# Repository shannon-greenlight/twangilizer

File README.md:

# Twangilizer - 4 Harmonic Tracking Oscillator with 4 VCAs
Twangilizer is a 20HP Eurorack module designed and made by Greenface Labs.
Used in conjunction with a VCO and a multiple-output CV generating module such as the Bonkulator, Twangilizer is a great way to set the amplitude envelopes of a tone and 4 of its harmonics. 
The harmonics are selectable from 1f, 2f, 3f, 4f, 5f, 6f, 7f and 8f. They are available as square waves at the output jacks 1-4.
The harmonics are also used to generate 10-step sine-wave approximations. The amplitudes of these waves are set by the CV inputs and then added to form the analog signal output.

Twangilizer features one signal input, an analog signal output, 4 digital harmonic outputs, 4 CV bias level adjustment pots, and four CV inputs to the VCAs.
It also features harmonic selection controls: Four 8 position rotary switches to select the harmonic from the above list. And there is a toggle switch per channel that selects divide by one, or divide by two.

The signal input level must be greater than .1Vp-p for the phase-locked loop circuits to be able to lock on.
The output signal ranges from 0 to 10Vp-p. The CV inputs range is 0 - 10V.

These repos contain the materials needed to construct the Twangilizer main board and the front panel. The files are for KiCAD 6.0. 
Go to the Greenlight Kicad repo to get the needed libraries. The gerber files work with JLCPC and will most likely work with other board manufacturers.

When using the JLCPCB assembly service, the BOM is split into 3 parts.
- bom/lcsc/main_bom.xlsx : The parts to be assembled by JLCPCB
- bom/digi-key/main_split.xlsx : The remaining parts to be assembled by user
- bom/other/other_bom.xlsx : The parts that must be bought from sources other than JLCPCB and Digi-Key

Also, when an assembly service is used, a component position file is required. This file's path is: fab/main_cpl.xlsx

notes: 	The cpl files are auto-generated from the .pos files produced by KiCAD. The bom files are generated by generate_boms.bat. You will need to refresh the data and save the file when changes to 
the schematic that affect the BOM or changes to the board layout occur. 
If they exist, the extra parts and additional data fields that appear on the schematic help to produce the different BOM files. 
They must be maintained for these BOMs to come out right.

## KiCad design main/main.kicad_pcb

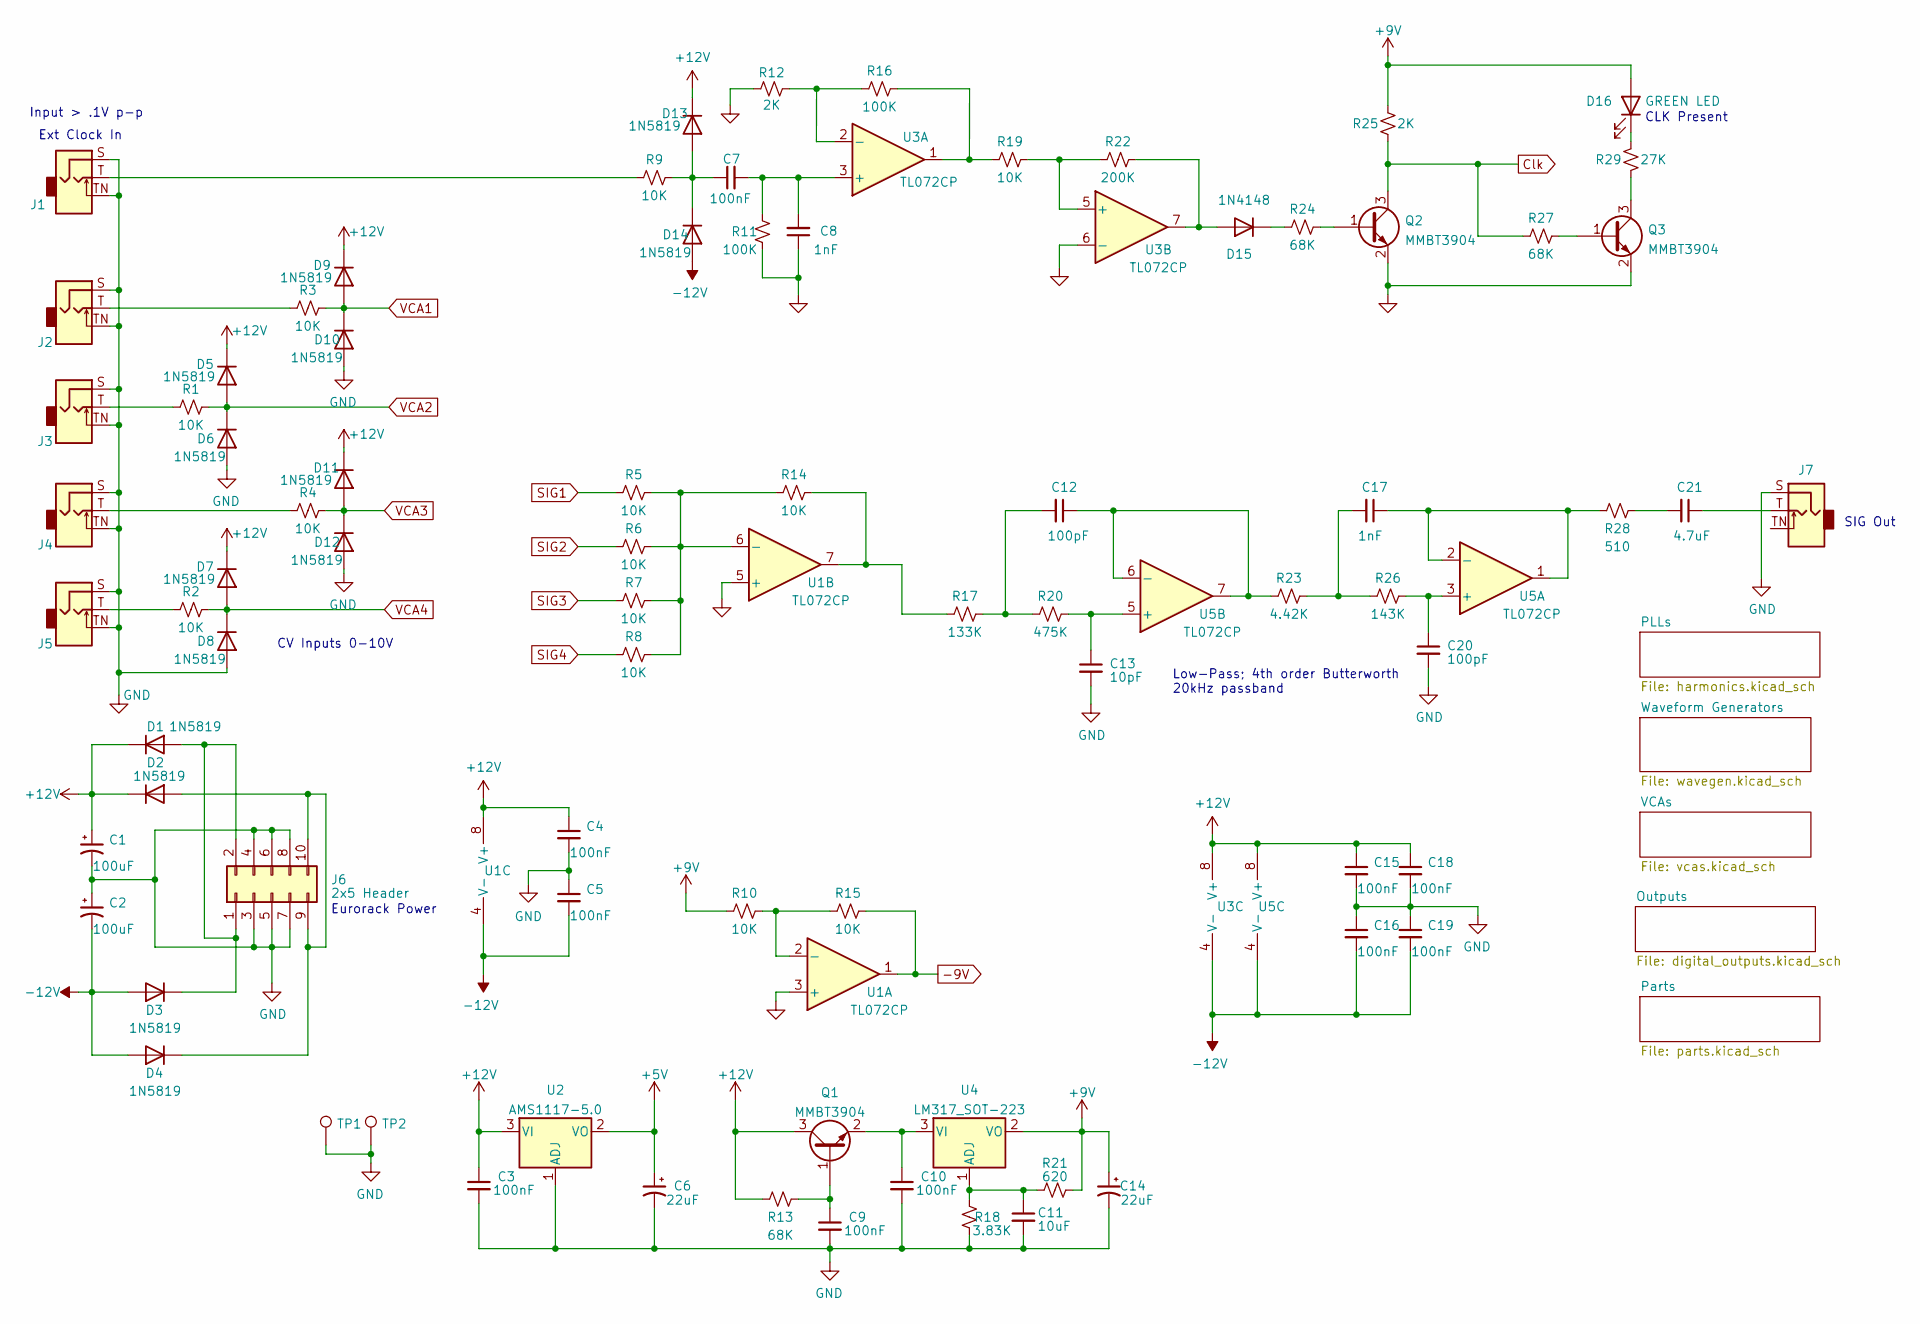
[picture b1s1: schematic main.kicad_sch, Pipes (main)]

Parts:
C1, C2: 100uF; CP_Elec_6.3x5.4_Nichicon; Digi-Key Part 399-EDH107M016A9GAACT-ND
C3, C4, C5, C7, C9, C10, C15, C16, C18, C19: 100nF; C_0805_2012Metric_Pad1.18x1.45mm_HandSolder; Digi-Key Part 478-10836-1-ND
C6, C14: 22uF; CP_EIA-3216-18_Kemet-A; Digi-Key Part 478-12960-1-ND
C8, C17: 1nF; C_0805_2012Metric_Pad1.18x1.45mm_HandSolder; Digi-Key Part 399-9877-1-ND
C11: 10uF; C_0805_2012Metric_Pad1.18x1.45mm_HandSolder; Digi-Key Part 399-9886-1-ND
C12, C20: 100pF; C_0805_2012Metric_Pad1.18x1.45mm_HandSolder; Digi-Key Part 399-9877-1-ND
C13: 10pF; C_0603_1608Metric_Pad1.08x0.95mm_HandSolder; Digi-Key Part 399-9877-1-ND
C21: 4.7uF; C_1206_3216Metric; Digi-Key Part 399-9877-1-ND
D1, D2, D3, D4, D5, D6, D7, D8, D9, D10, D11, D12, D13, D14: 1N5819; D_SOD-323_HandSoldering; Digi-Key Part 478-7800-1-ND
D15: 1N4148; D_SOD-123; Digi-Key Part 1N4148VSCT-ND
D16: GREEN LED; LED_D3.0mm; Digi-Key Part 732-5007-ND
J1, J2, J3, J4, J5, J7: 3.5mm Jack; Jack_3.5mm_QingPu_WQP-PJ398SM_Vertical; Digi-Key Part WM17366-ND
J6: 2x5 Header; PinHeader_2x05_P2.54mm_Vertical_SMD; LCSC Part # C124391
Q1, Q2, Q3: MMBT3904; SOT-23; LCSC Part # C20526
R1, R2, R3, R4, R5, R6, R7, R8, R9, R10, R14, R15, R19: 10K; R_0603_1608Metric; Digi-Key Part CRT0805-FZ-1002ELFCT-ND
R11, R16: 100K; R_0805_2012Metric_Pad1.20x1.40mm_HandSolder; Digi-Key Part CF14JT10K0CT-ND
R12, R25: 2K; R_0603_1608Metric; Digi-Key Part CRT0805-FZ-1002ELFCT-ND
R13: 68K; R_0805_2012Metric_Pad1.20x1.40mm_HandSolder; Digi-Key Part CF14JT68K0CT-ND
R17: 133K; R_0603_1608Metric; Digi-Key Part CRT0805-FZ-1002ELFCT-ND
R18: 3.83K; R_0805_2012Metric_Pad1.20x1.40mm_HandSolder; Digi-Key Part CF14JT68K0CT-ND
R20: 475K; R_0603_1608Metric; Digi-Key Part CRT0805-FZ-1002ELFCT-ND
R21: 620; R_0805_2012Metric_Pad1.20x1.40mm_HandSolder; Digi-Key Part CF14JT68K0CT-ND
R22: 200K; R_0805_2012Metric_Pad1.20x1.40mm_HandSolder; Digi-Key Part CF14JT10K0CT-ND
R23: 4.42K; R_0603_1608Metric; Digi-Key Part CRT0805-FZ-1002ELFCT-ND
R24, R27: 68K; R_0805_2012Metric_Pad1.20x1.40mm_HandSolder; Digi-Key Part CF14JT10K0CT-ND
R26: 143K; R_0603_1608Metric; Digi-Key Part CRT0805-FZ-1002ELFCT-ND
R28: 510; R_0805_2012Metric_Pad1.20x1.40mm_HandSolder; Digi-Key Part PPC470W-1CT-ND
R29: 27K; R_0805_2012Metric_Pad1.20x1.40mm_HandSolder; Digi-Key Part CRT0805-FZ-1002ELFCT-ND
TP1, TP2: TestPoint; TestPoint_Keystone_5005-5009_Compact; Digi-Key Part 36-5006-ND
U1, U3, U5: TL072CP; SOIC-8_3.9x4.9mm_P1.27mm; Digi-Key Part 296-1775-5-ND
U2: AMS1117-5.0; SOT-223-3_TabPin2; LCSC Part # C6187
U4: LM317_SOT-223; SOT-223-3_TabPin2; LCSC Part # C347367

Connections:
+5V: C6.1, U2.2 (VO); also elsewhere on the board
+9V: C14.1, D16.2 (A), R10.2, R21.1, R25.1, U4.2 (VO); also elsewhere on the board
+12V: C1.1, C3.1, C4.1, C15.1, C18.1, D1.1 (K), D2.1 (K), D5.1 (K), D7.1 (K), D9.1 (K), D11.1 (K), D13.1 (K), Q1.3 (C), R13.2, U1.8 (V+), U2.3 (VI), U3.8 (V+), U5.8 (V+); also elsewhere on the board
-9V: R15.1, U1.1; also elsewhere on the board
-12V: C2.2, C5.2, C16.2, C19.2, D3.2 (A), D4.2 (A), D14.2 (A), U1.4 (V-), U3.4 (V-), U5.4 (V-); also elsewhere on the board
Clk: Q2.3 (C), R25.2, R27.2; also elsewhere on the board
GND: C1.2, C2.1, C3.2, C4.2, C5.1, C6.2, C8.1, C9.2, C10.2, C11.2, C13.2, C14.2, C15.2, C16.1, C18.2, C19.1, C20.2, D6.2 (A), D8.2 (A), D10.2 (A), D12.2 (A), J1.S, J1.TN, J2.S, J2.TN, J3.S, J3.TN, J4.S, J4.TN, J5.S, J5.TN, J6.3, J6.4, J6.5, J6.6, J6.7, J6.8, J7.S, Q2.2 (E), Q3.2 (E), R11.2, R12.1, R18.2, TP1.1, TP2.1, U1.3 (+), U1.5 (+), U2.1 (ADJ), U3.6 (-); also elsewhere on the board
unnamed: C7.1, D13.2 (A), D14.1 (K), R9.1
unnamed: C7.2, C8.2, R11.1, U3.3 (+)
unnamed: C9.1, Q1.1 (B), R13.1
unnamed: C10.1, Q1.2 (E), U4.3 (VI)
unnamed: C11.1, R18.1, R21.2, U4.1 (ADJ)
unnamed: C12.1, R23.2, U5.6 (-), U5.7
unnamed: C12.2, R17.1, R20.2
unnamed: C13.1, R20.1, U5.5 (+)
unnamed: C17.1, R28.1, U5.1, U5.2 (-)
unnamed: C17.2, R23.1, R26.2
unnamed: C20.1, R26.1, U5.3 (+)
unnamed: C21.1, J7.T
unnamed: C21.2, R28.2
unnamed: D1.2 (A), D3.1 (K), J6.1, J6.2
unnamed: D2.2 (A), D4.1 (K), J6.9, J6.10
unnamed: D15.1 (K), R24.2
unnamed: D15.2 (A), R22.1, U3.7
unnamed: D16.1 (K), R29.2
unnamed: J1.T, R9.2
unnamed: J2.T, R3.2
unnamed: J3.T, R1.2
unnamed: J4.T, R4.2
unnamed: J5.T, R2.2
unnamed: Q2.1 (B), R24.1
unnamed: Q3.1 (B), R27.1
unnamed: Q3.3 (C), R29.1
unnamed: R10.1, R15.2, U1.2 (-)
unnamed: R12.2, R16.2, U3.2 (-)
unnamed: R14.1, R17.2, U1.7
unnamed: R5.1, R6.1, R7.1, R8.1, R14.2, U1.6 (-)
unnamed: R16.1, R19.2, U3.1
unnamed: R19.1, R22.2, U3.5 (+)
SIG1: R5.2; also elsewhere on the board
SIG2: R6.2; also elsewhere on the board
SIG3: R7.2; also elsewhere on the board
SIG4: R8.2; also elsewhere on the board
VCA1: D9.2 (A), D10.1 (K), R3.1; also elsewhere on the board
VCA2: D5.2 (A), D6.1 (K), R1.1; also elsewhere on the board
VCA3: D11.2 (A), D12.1 (K), R4.1; also elsewhere on the board
VCA4: D7.2 (A), D8.1 (K), R2.1; also elsewhere on the board

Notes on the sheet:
Eurorack Power
SIG Out
Low-Pass; 4th order Butterworth 20kHz passband
Input > .1V p-p
CLK Present
CV Inputs 0-10V
Ext Clock In

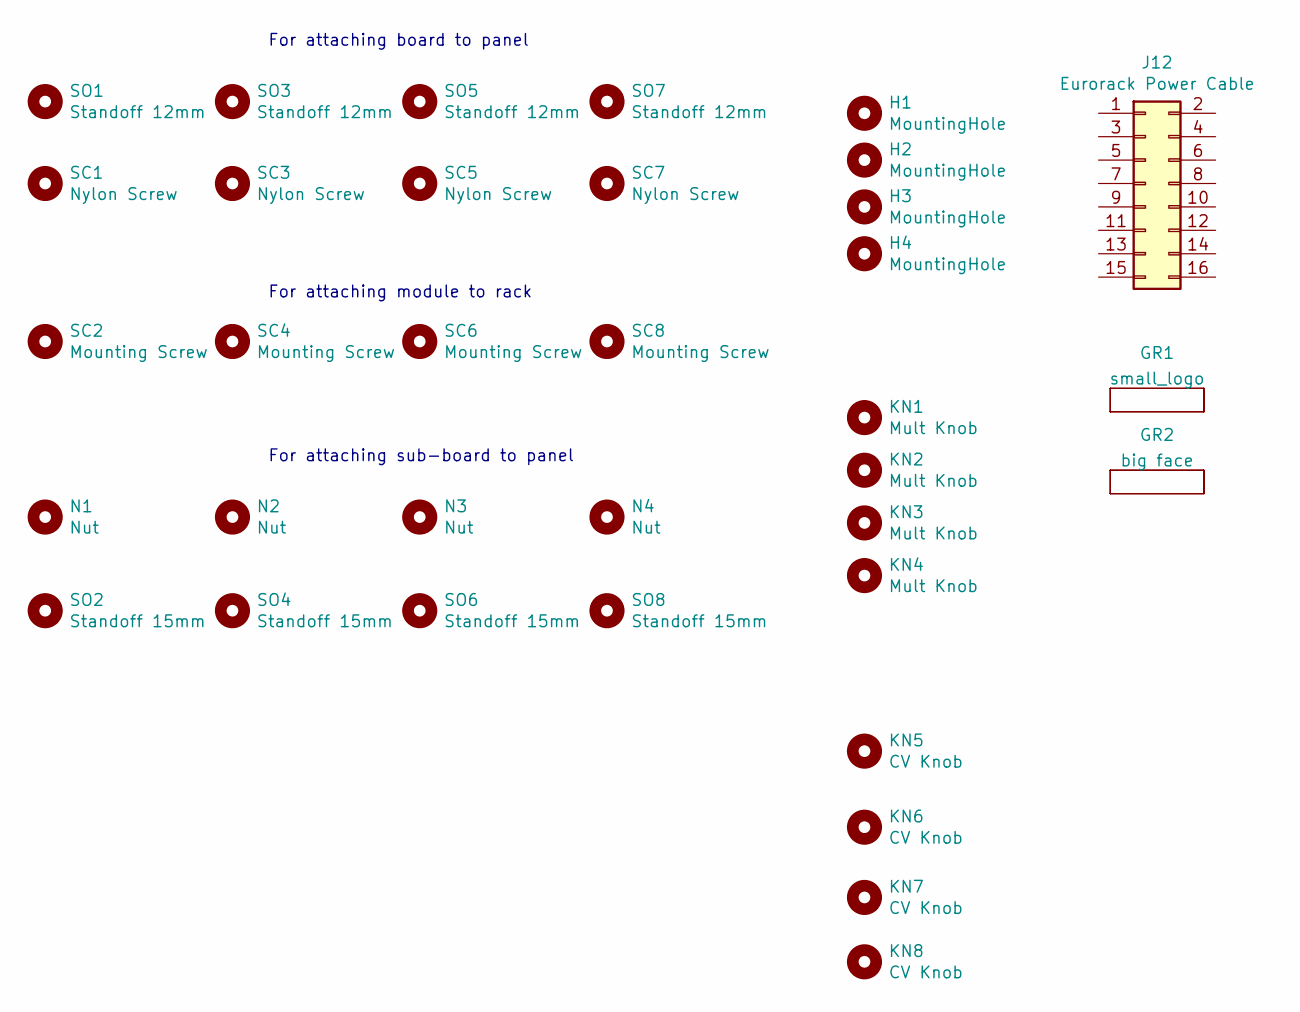
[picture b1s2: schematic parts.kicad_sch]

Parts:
GR1: small_logo; small_face
GR2: big face; face_logo
H1, H2, H3, H4: MountingHole; MountingHole_2.5mm
J12: Eurorack Power Cable; Digi-Key Part H3CCS-1618G-ND
KN1, KN2, KN3, KN4: Mult Knob; Digi-Key Part 1722-1314-ND
KN5, KN6, KN7, KN8: CV Knob; Digi-Key Part 4654-FC7251-ND
N1, N2, N3, N4: Nut; Digi-Key Part 36-4687-ND
SC1, SC3, SC5, SC7: Nylon Screw; Digi-Key Part 36-29331-ND
SC2, SC4, SC6, SC8: Mounting Screw; Digi-Key Part 335-1156-ND
SO1, SO3, SO5, SO7: Standoff 12mm; Digi-Key Part 732-13063-ND
SO2, SO4, SO6, SO8: Standoff 15mm; Digi-Key Part 732-13072-ND

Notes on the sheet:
For attaching module to rack
For attaching board to panel
For attaching sub-board to panel

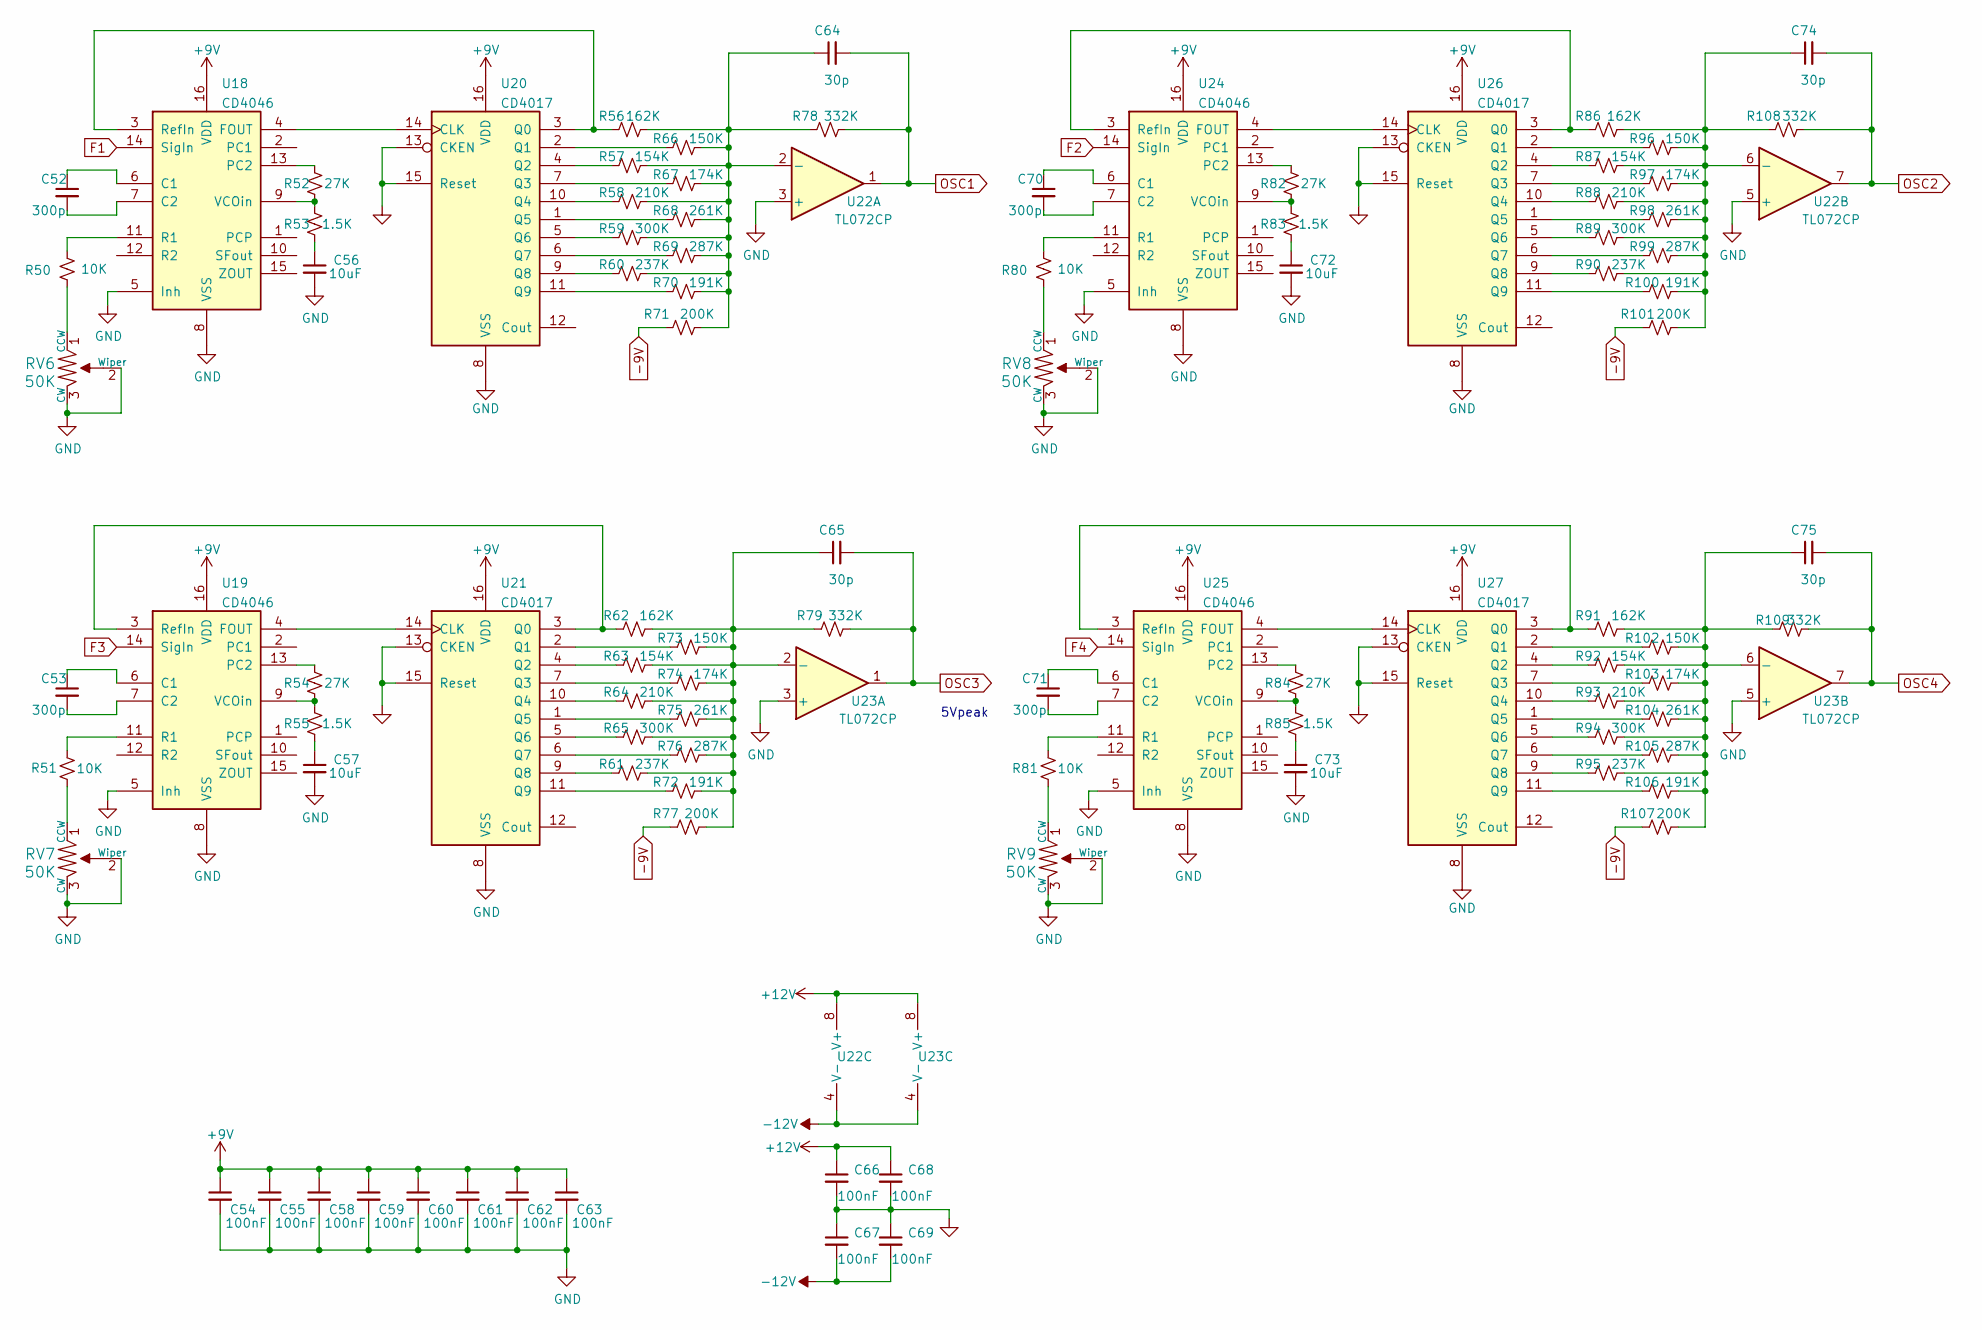
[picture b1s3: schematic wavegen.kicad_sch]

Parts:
C52, C53, C70, C71: 300p; C_0603_1608Metric_Pad1.08x0.95mm_HandSolder; Digi-Key Part BC2662CT-ND
C54, C55, C58, C59, C60, C61, C62, C63, C66, C67, C68, C69: 100nF; C_0805_2012Metric_Pad1.18x1.45mm_HandSolder; Digi-Key Part 478-10836-1-ND
C56, C57, C72, C73: 10uF; C_0805_2012Metric_Pad1.18x1.45mm_HandSolder; Digi-Key Part 478-10836-1-ND
C64, C65, C74, C75: 30p; C_0603_1608Metric_Pad1.08x0.95mm_HandSolder; Digi-Key Part BC2662CT-ND
R50, R51, R80, R81: 10K; R_0603_1608Metric; Digi-Key Part CF14JT10K0CT-ND
R52, R54, R82, R84: 27K; R_0805_2012Metric_Pad1.20x1.40mm_HandSolder; Digi-Key Part CF14JT10K0CT-ND
R53, R55, R83, R85: 1.5K; R_0805_2012Metric_Pad1.20x1.40mm_HandSolder; Digi-Key Part CF14JT10K0CT-ND
R56, R62, R86, R91: 162K; R_0603_1608Metric; Digi-Key Part CF14JT10K0CT-ND
R57, R63, R87, R92: 154K; R_0603_1608Metric; Digi-Key Part CF14JT10K0CT-ND
R58, R64, R88, R93: 210K; R_0603_1608Metric; Digi-Key Part CF14JT10K0CT-ND
R59, R65, R89, R94: 300K; R_0603_1608Metric; Digi-Key Part CF14JT10K0CT-ND
R60, R61, R90, R95: 237K; R_0603_1608Metric; Digi-Key Part CF14JT10K0CT-ND
R66, R73, R96, R102: 150K; R_0603_1608Metric; Digi-Key Part CF14JT10K0CT-ND
R67, R74, R97, R103: 174K; R_0603_1608Metric; Digi-Key Part CF14JT10K0CT-ND
R68, R75, R98, R104: 261K; R_0603_1608Metric; Digi-Key Part CF14JT10K0CT-ND
R69, R76, R99, R105: 287K; R_0603_1608Metric; Digi-Key Part CF14JT10K0CT-ND
R70, R72, R100, R106: 191K; R_0603_1608Metric; Digi-Key Part CF14JT10K0CT-ND
R71, R77, R101, R107: 200K; R_0603_1608Metric; Digi-Key Part CF14JT10K0CT-ND
R78, R79, R108, R109: 332K; R_0603_1608Metric; Digi-Key Part CF14JT10K0CT-ND
RV6, RV7, RV8, RV9: 50K; Potentiometer_Bourns_3224W_Vertical; Digi-Key Part 490-2881-ND
U18, U19, U24, U25: CD4046; TSSOP-16_4.4x5mm_P0.65mm; LCSC Part # C2651240
U20, U21, U26, U27: CD4017; SOIC-16_3.9x9.9mm_P1.27mm; Digi-Key Part 296-12808-1-ND
U22, U23: TL072CP; SOIC-8_3.9x4.9mm_P1.27mm; Digi-Key Part 296-1775-5-ND

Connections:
+9V: C54.1, C55.1, C58.1, C59.1, C60.1, C61.1, C62.1, C63.1, U18.16 (VDD), U19.16 (VDD), U20.16 (VDD), U21.16 (VDD), U24.16 (VDD), U25.16 (VDD), U26.16 (VDD), U27.16 (VDD); also elsewhere on the board
+12V: C66.1, C68.1, U22.8 (V+), U23.8 (V+); also elsewhere on the board
-9V: R71.1, R77.1, R101.1, R107.1; also elsewhere on the board
-12V: C67.2, C69.2, U22.4 (V-), U23.4 (V-); also elsewhere on the board
F1: U18.14 (SigIn); also elsewhere on the board
F2: U24.14 (SigIn); also elsewhere on the board
F3: U19.14 (SigIn); also elsewhere on the board
F4: U25.14 (SigIn); also elsewhere on the board
GND: C54.2, C55.2, C56.2, C57.2, C58.2, C59.2, C60.2, C61.2, C62.2, C63.2, C66.2, C67.1, C68.2, C69.1, C72.2, C73.2, RV6.2 (Wiper), RV6.3 (CW), RV7.2 (Wiper), RV7.3 (CW), RV8.2 (Wiper), RV8.3 (CW), RV9.2 (Wiper), RV9.3 (CW), U18.5 (Inh), U18.8 (VSS), U19.5 (Inh), U19.8 (VSS), U20.8 (VSS), U20.13 (CKEN), U20.15 (Reset), U21.8 (VSS), U21.13 (CKEN), U21.15 (Reset), U22.3 (+), U22.5 (+), U23.3 (+), U23.5 (+), U24.5 (Inh), U24.8 (VSS), U25.5 (Inh), U25.8 (VSS), U26.8 (VSS), U26.13 (CKEN), U26.15 (Reset), U27.8 (VSS), U27.13 (CKEN), U27.15 (Reset); also elsewhere on the board
unnamed: C52.1, U18.6 (C1)
unnamed: C52.2, U18.7 (C2)
unnamed: C53.1, U19.6 (C1)
unnamed: C53.2, U19.7 (C2)
unnamed: C56.1, R53.2
unnamed: C57.1, R55.2
unnamed: C64.1, R56.2, R57.2, R58.2, R59.2, R60.2, R66.2, R67.2, R68.2, R69.2, R70.2, R71.2, R78.1, U22.2 (-)
unnamed: C65.1, R61.2, R62.2, R63.2, R64.2, R65.2, R72.2, R73.2, R74.2, R75.2, R76.2, R77.2, R79.1, U23.2 (-)
unnamed: C70.1, U24.6 (C1)
unnamed: C70.2, U24.7 (C2)
unnamed: C71.1, U25.6 (C1)
unnamed: C71.2, U25.7 (C2)
unnamed: C72.1, R83.2
unnamed: C73.1, R85.2
unnamed: C74.1, R86.2, R87.2, R88.2, R89.2, R90.2, R96.2, R97.2, R98.2, R99.2, R100.2, R101.2, R108.1, U22.6 (-)
unnamed: C75.1, R91.2, R92.2, R93.2, R94.2, R95.2, R102.2, R103.2, R104.2, R105.2, R106.2, R107.2, R109.1, U23.6 (-)
unnamed: R50.1, U18.11 (R1)
unnamed: R50.2, RV6.1 (CCW)
unnamed: R51.1, U19.11 (R1)
unnamed: R51.2, RV7.1 (CCW)
unnamed: R52.1, U18.13 (PC2)
unnamed: R52.2, R53.1, U18.9 (VCOin)
unnamed: R54.1, U19.13 (PC2)
unnamed: R54.2, R55.1, U19.9 (VCOin)
unnamed: R56.1, U18.3 (RefIn), U20.3 (Q0)
unnamed: R57.1, U20.4 (Q2)
unnamed: R58.1, U20.10 (Q4)
unnamed: R59.1, U20.5 (Q6)
unnamed: R60.1, U20.9 (Q8)
unnamed: R61.1, U21.9 (Q8)
unnamed: R62.1, U19.3 (RefIn), U21.3 (Q0)
unnamed: R63.1, U21.4 (Q2)
unnamed: R64.1, U21.10 (Q4)
unnamed: R65.1, U21.5 (Q6)
unnamed: R66.1, U20.2 (Q1)
unnamed: R67.1, U20.7 (Q3)
unnamed: R68.1, U20.1 (Q5)
unnamed: R69.1, U20.6 (Q7)
unnamed: R70.1, U20.11 (Q9)
unnamed: R72.1, U21.11 (Q9)
unnamed: R73.1, U21.2 (Q1)
unnamed: R74.1, U21.7 (Q3)
unnamed: R75.1, U21.1 (Q5)
unnamed: R76.1, U21.6 (Q7)
unnamed: R80.1, U24.11 (R1)
unnamed: R80.2, RV8.1 (CCW)
unnamed: R81.1, U25.11 (R1)
unnamed: R81.2, RV9.1 (CCW)
unnamed: R82.1, U24.13 (PC2)
unnamed: R82.2, R83.1, U24.9 (VCOin)
unnamed: R84.1, U25.13 (PC2)
unnamed: R84.2, R85.1, U25.9 (VCOin)
unnamed: R86.1, U24.3 (RefIn), U26.3 (Q0)
unnamed: R87.1, U26.4 (Q2)
unnamed: R88.1, U26.10 (Q4)
unnamed: R89.1, U26.5 (Q6)
unnamed: R90.1, U26.9 (Q8)
unnamed: R91.1, U25.3 (RefIn), U27.3 (Q0)
unnamed: R92.1, U27.4 (Q2)
unnamed: R93.1, U27.10 (Q4)
unnamed: R94.1, U27.5 (Q6)
unnamed: R95.1, U27.9 (Q8)
unnamed: R96.1, U26.2 (Q1)
unnamed: R97.1, U26.7 (Q3)
unnamed: R98.1, U26.1 (Q5)
unnamed: R99.1, U26.6 (Q7)
unnamed: R100.1, U26.11 (Q9)
unnamed: R102.1, U27.2 (Q1)
unnamed: R103.1, U27.7 (Q3)
unnamed: R104.1, U27.1 (Q5)
unnamed: R105.1, U27.6 (Q7)
unnamed: R106.1, U27.11 (Q9)
unnamed: U18.4 (FOUT), U20.14 (CLK)
unnamed: U19.4 (FOUT), U21.14 (CLK)
unnamed: U24.4 (FOUT), U26.14 (CLK)
unnamed: U25.4 (FOUT), U27.14 (CLK)
OSC1: C64.2, R78.2, U22.1; also elsewhere on the board
OSC2: C74.2, R108.2, U22.7; also elsewhere on the board
OSC3: C65.2, R79.2, U23.1; also elsewhere on the board
OSC4: C75.2, R109.2, U23.7; also elsewhere on the board

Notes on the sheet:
5Vpeak

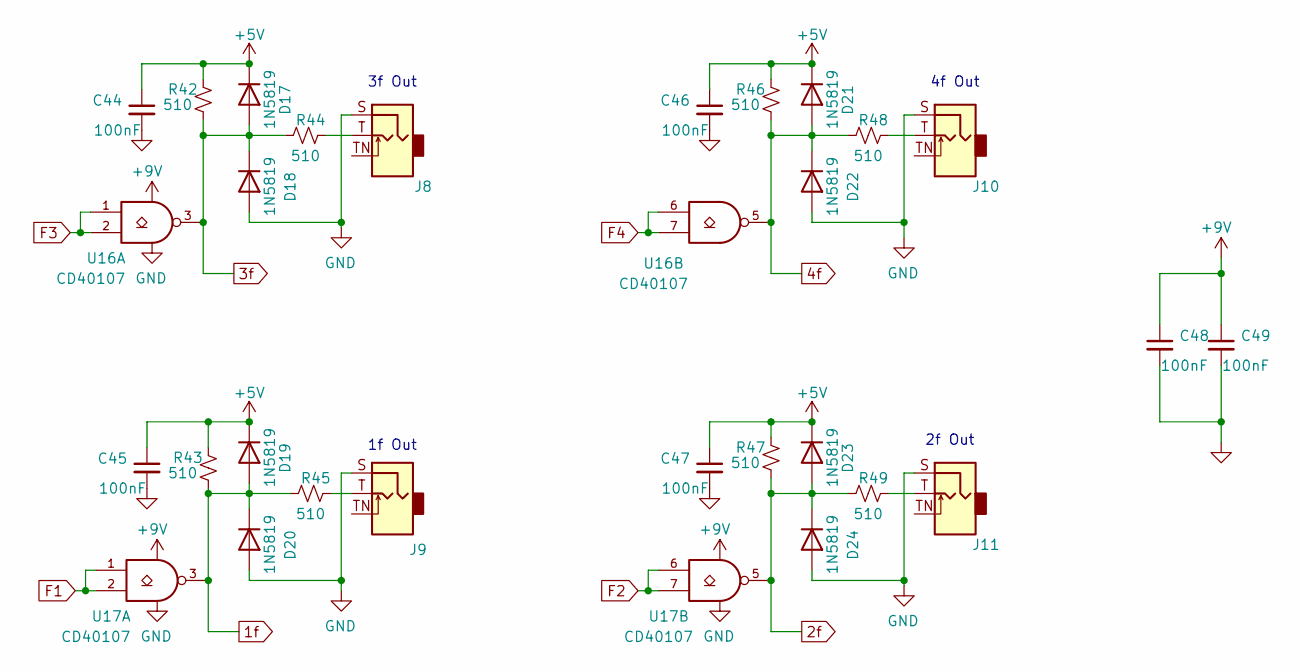
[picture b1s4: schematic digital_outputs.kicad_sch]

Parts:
C44, C45, C46, C47, C48, C49: 100nF; C_0805_2012Metric_Pad1.18x1.45mm_HandSolder; Digi-Key Part 478-10836-1-ND
D17, D18, D19, D20, D21, D22, D23, D24: 1N5819; D_SOD-323_HandSoldering; Digi-Key Part 478-7800-1-ND
J8, J9, J10, J11: 3.5mm Jack; Jack_3.5mm_QingPu_WQP-PJ398SM_Vertical; Digi-Key Part WM17366-ND
R42, R43, R46, R47: 510; R_0805_2012Metric_Pad1.20x1.40mm_HandSolder; Digi-Key Part PPC470W-1CT-ND
R44, R45, R48, R49: 510; R_0805_2012Metric_Pad1.20x1.40mm_HandSolder; Digi-Key Part CRT0805-FZ-1002ELFCT-ND
U16, U17: CD40107; SOIC-8_3.9x4.9mm_P1.27mm; LCSC Part # C2691402

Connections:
1f: D19.2 (A), D20.1 (K), R43.1, R45.2, U17.3
2f: D23.2 (A), D24.1 (K), R47.1, R49.2, U17.5
3f: D17.2 (A), D18.1 (K), R42.1, R44.2, U16.3
4f: D21.2 (A), D22.1 (K), R46.1, R48.2, U16.5
+5V: C44.1, C45.1, C46.1, C47.1, D17.1 (K), D19.1 (K), D21.1 (K), D23.1 (K), R42.2, R43.2, R46.2, R47.2; also elsewhere on the board
+9V: C48.1, C49.1, U16.8 (VCC), U17.8 (VCC); also elsewhere on the board
F1: U17.1, U17.2; also elsewhere on the board
F2: U17.6, U17.7; also elsewhere on the board
F3: U16.1, U16.2; also elsewhere on the board
F4: U16.6, U16.7; also elsewhere on the board
GND: C44.2, C45.2, C46.2, C47.2, C48.2, C49.2, D18.2 (A), D20.2 (A), D22.2 (A), D24.2 (A), J8.S, J9.S, J10.S, J11.S, U16.4 (GND), U17.4 (GND); also elsewhere on the board
unnamed: J8.T, R44.1
unnamed: J9.T, R45.1
unnamed: J10.T, R48.1
unnamed: J11.T, R49.1

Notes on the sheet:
2f Out
4f Out
3f Out
1f Out

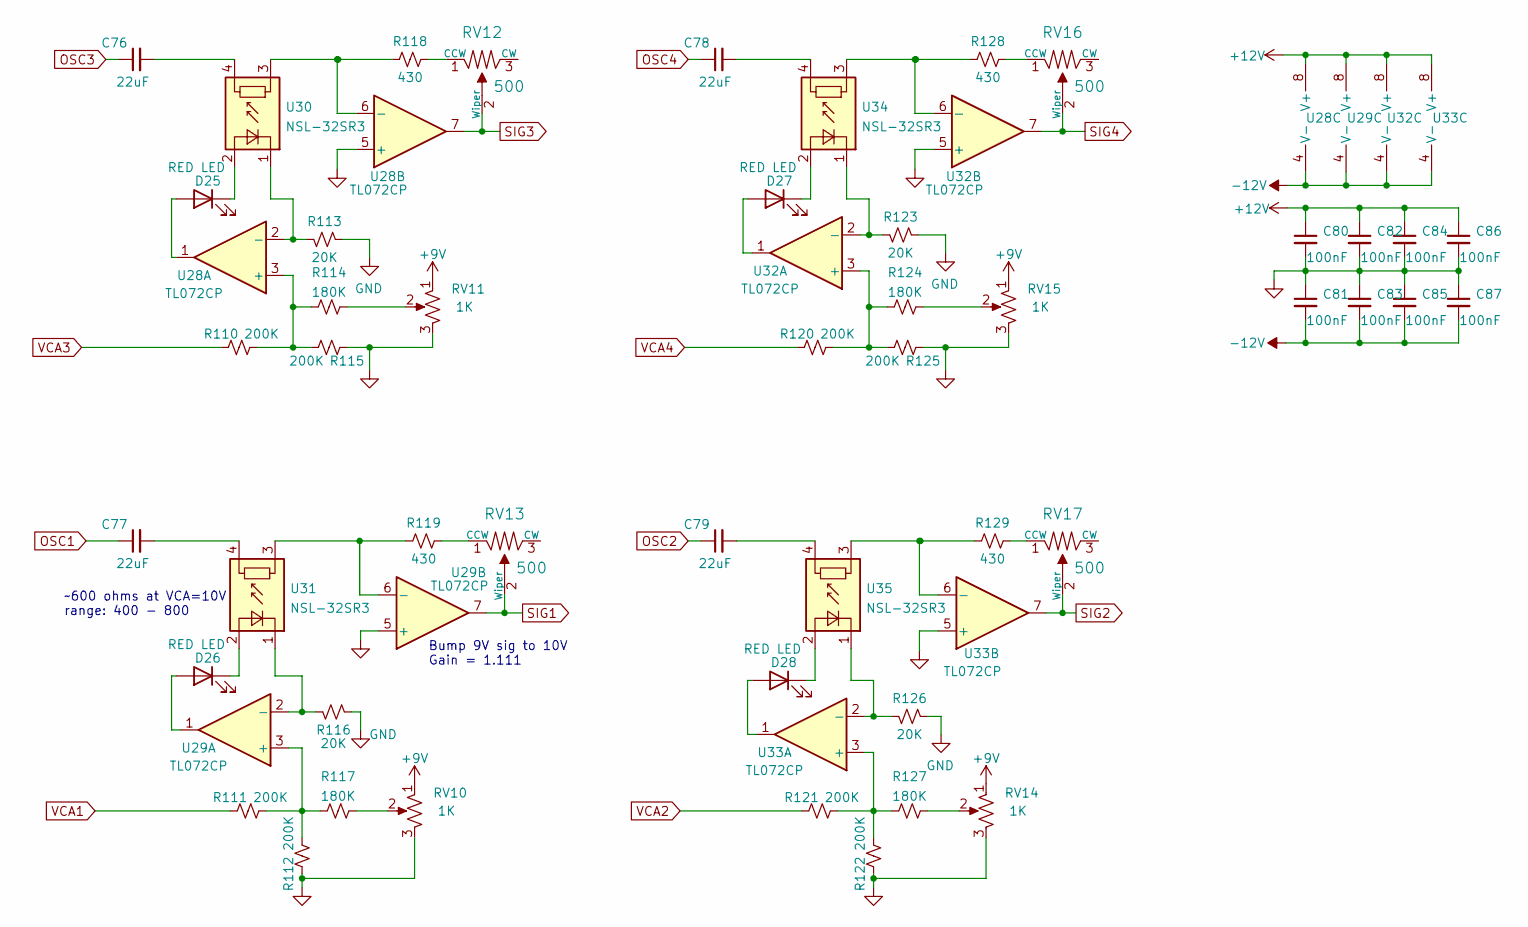
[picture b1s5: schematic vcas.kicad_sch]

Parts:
C76, C77, C78, C79: 22uF; C_0805_2012Metric_Pad1.18x1.45mm_HandSolder; Digi-Key Part 478-10836-1-ND
C80, C81, C82, C83, C84, C85, C86, C87: 100nF; C_0805_2012Metric_Pad1.18x1.45mm_HandSolder; Digi-Key Part 478-10836-1-ND
D25, D26, D27, D28: RED LED; LED_D3.0mm; Digi-Key Part 732-5005-ND
R110, R111, R112, R115, R120, R121, R122, R125: 200K; R_0603_1608Metric; Digi-Key Part CF14JT10K0CT-ND
R113, R116, R123, R126: 20K; R_0603_1608Metric; Digi-Key Part CRT0805-FZ-1002ELFCT-ND
R114, R117, R124, R127: 180K; R_0603_1608Metric; LCSC Part # C3016400
R118, R119, R128, R129: 430; R_0603_1608Metric; Digi-Key Part CRT0805-FZ-1002ELFCT-ND
RV10, RV11, RV14, RV15: 1K; Potentiometer_Bourns_PTV09A-1_Single_Vertical; Digi-Key Part PTV09A-4225F-B102-ND
RV12, RV13, RV16, RV17: 500; Potentiometer_Bourns_3224W_Vertical; LCSC Part # C116324
U28: TL072CP; SOIC-8_3.9x4.9mm_P1.27mm; LCSC Part # C6961
U29, U32, U33: TL072CP; SOIC-8_3.9x4.9mm_P1.27mm; Digi-Key Part 296-1775-5-ND
U30, U31, U34, U35: NSL-32SR3; Digi-Key Part NSL-32SR3-ND

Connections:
+9V: RV10.1, RV11.1, RV14.1, RV15.1; also elsewhere on the board
+12V: C80.1, C82.1, C84.1, C86.1, U28.8 (V+), U29.8 (V+), U32.8 (V+), U33.8 (V+); also elsewhere on the board
-12V: C81.2, C83.2, C85.2, C87.2, U28.4 (V-), U29.4 (V-), U32.4 (V-), U33.4 (V-); also elsewhere on the board
GND: C80.2, C81.1, C82.2, C83.1, C84.2, C85.1, C86.2, C87.1, R112.1, R113.2, R115.1, R116.2, R122.1, R123.2, R125.1, R126.2, RV10.3, RV11.3, RV14.3, RV15.3, U28.5 (+), U29.5 (+), U32.5 (+), U33.5 (+); also elsewhere on the board
unnamed: C76.2, U30.4
unnamed: C77.2, U31.4
unnamed: C78.2, U34.4
unnamed: C79.2, U35.4
unnamed: D25.1 (K), U30.2 (+)
unnamed: D25.2 (A), U28.1
unnamed: D26.1 (K), U31.2 (+)
unnamed: D26.2 (A), U29.1
unnamed: D27.1 (K), U34.2 (+)
unnamed: D27.2 (A), U32.1
unnamed: D28.1 (K), U35.2 (+)
unnamed: D28.2 (A), U33.1
unnamed: R110.2, R114.1, R115.2, U28.3 (+)
unnamed: R111.2, R112.2, R117.1, U29.3 (+)
unnamed: R113.1, U28.2 (-), U30.1 (-)
unnamed: R114.2, RV11.2
unnamed: R116.1, U29.2 (-), U31.1 (-)
unnamed: R117.2, RV10.2
unnamed: R118.1, RV12.1 (CCW)
unnamed: R118.2, U28.6 (-), U30.3
unnamed: R119.1, RV13.1 (CCW)
unnamed: R119.2, U29.6 (-), U31.3
unnamed: R120.2, R124.1, R125.2, U32.3 (+)
unnamed: R121.2, R122.2, R127.1, U33.3 (+)
unnamed: R123.1, U32.2 (-), U34.1 (-)
unnamed: R124.2, RV15.2
unnamed: R126.1, U33.2 (-), U35.1 (-)
unnamed: R127.2, RV14.2
unnamed: R128.1, RV16.1 (CCW)
unnamed: R128.2, U32.6 (-), U34.3
unnamed: R129.1, RV17.1 (CCW)
unnamed: R129.2, U33.6 (-), U35.3
OSC1: C77.1; also elsewhere on the board
OSC2: C79.1; also elsewhere on the board
OSC3: C76.1; also elsewhere on the board
OSC4: C78.1; also elsewhere on the board
SIG1: RV13.2 (Wiper), U29.7; also elsewhere on the board
SIG2: RV17.2 (Wiper), U33.7; also elsewhere on the board
SIG3: RV12.2 (Wiper), U28.7; also elsewhere on the board
SIG4: RV16.2 (Wiper), U32.7; also elsewhere on the board
VCA1: R111.1; also elsewhere on the board
VCA2: R121.1; also elsewhere on the board
VCA3: R110.1; also elsewhere on the board
VCA4: R120.1; also elsewhere on the board

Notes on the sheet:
Bump 9V sig to 10V Gain = 1.111
~600 ohms at VCA=10V range: 400 - 800
